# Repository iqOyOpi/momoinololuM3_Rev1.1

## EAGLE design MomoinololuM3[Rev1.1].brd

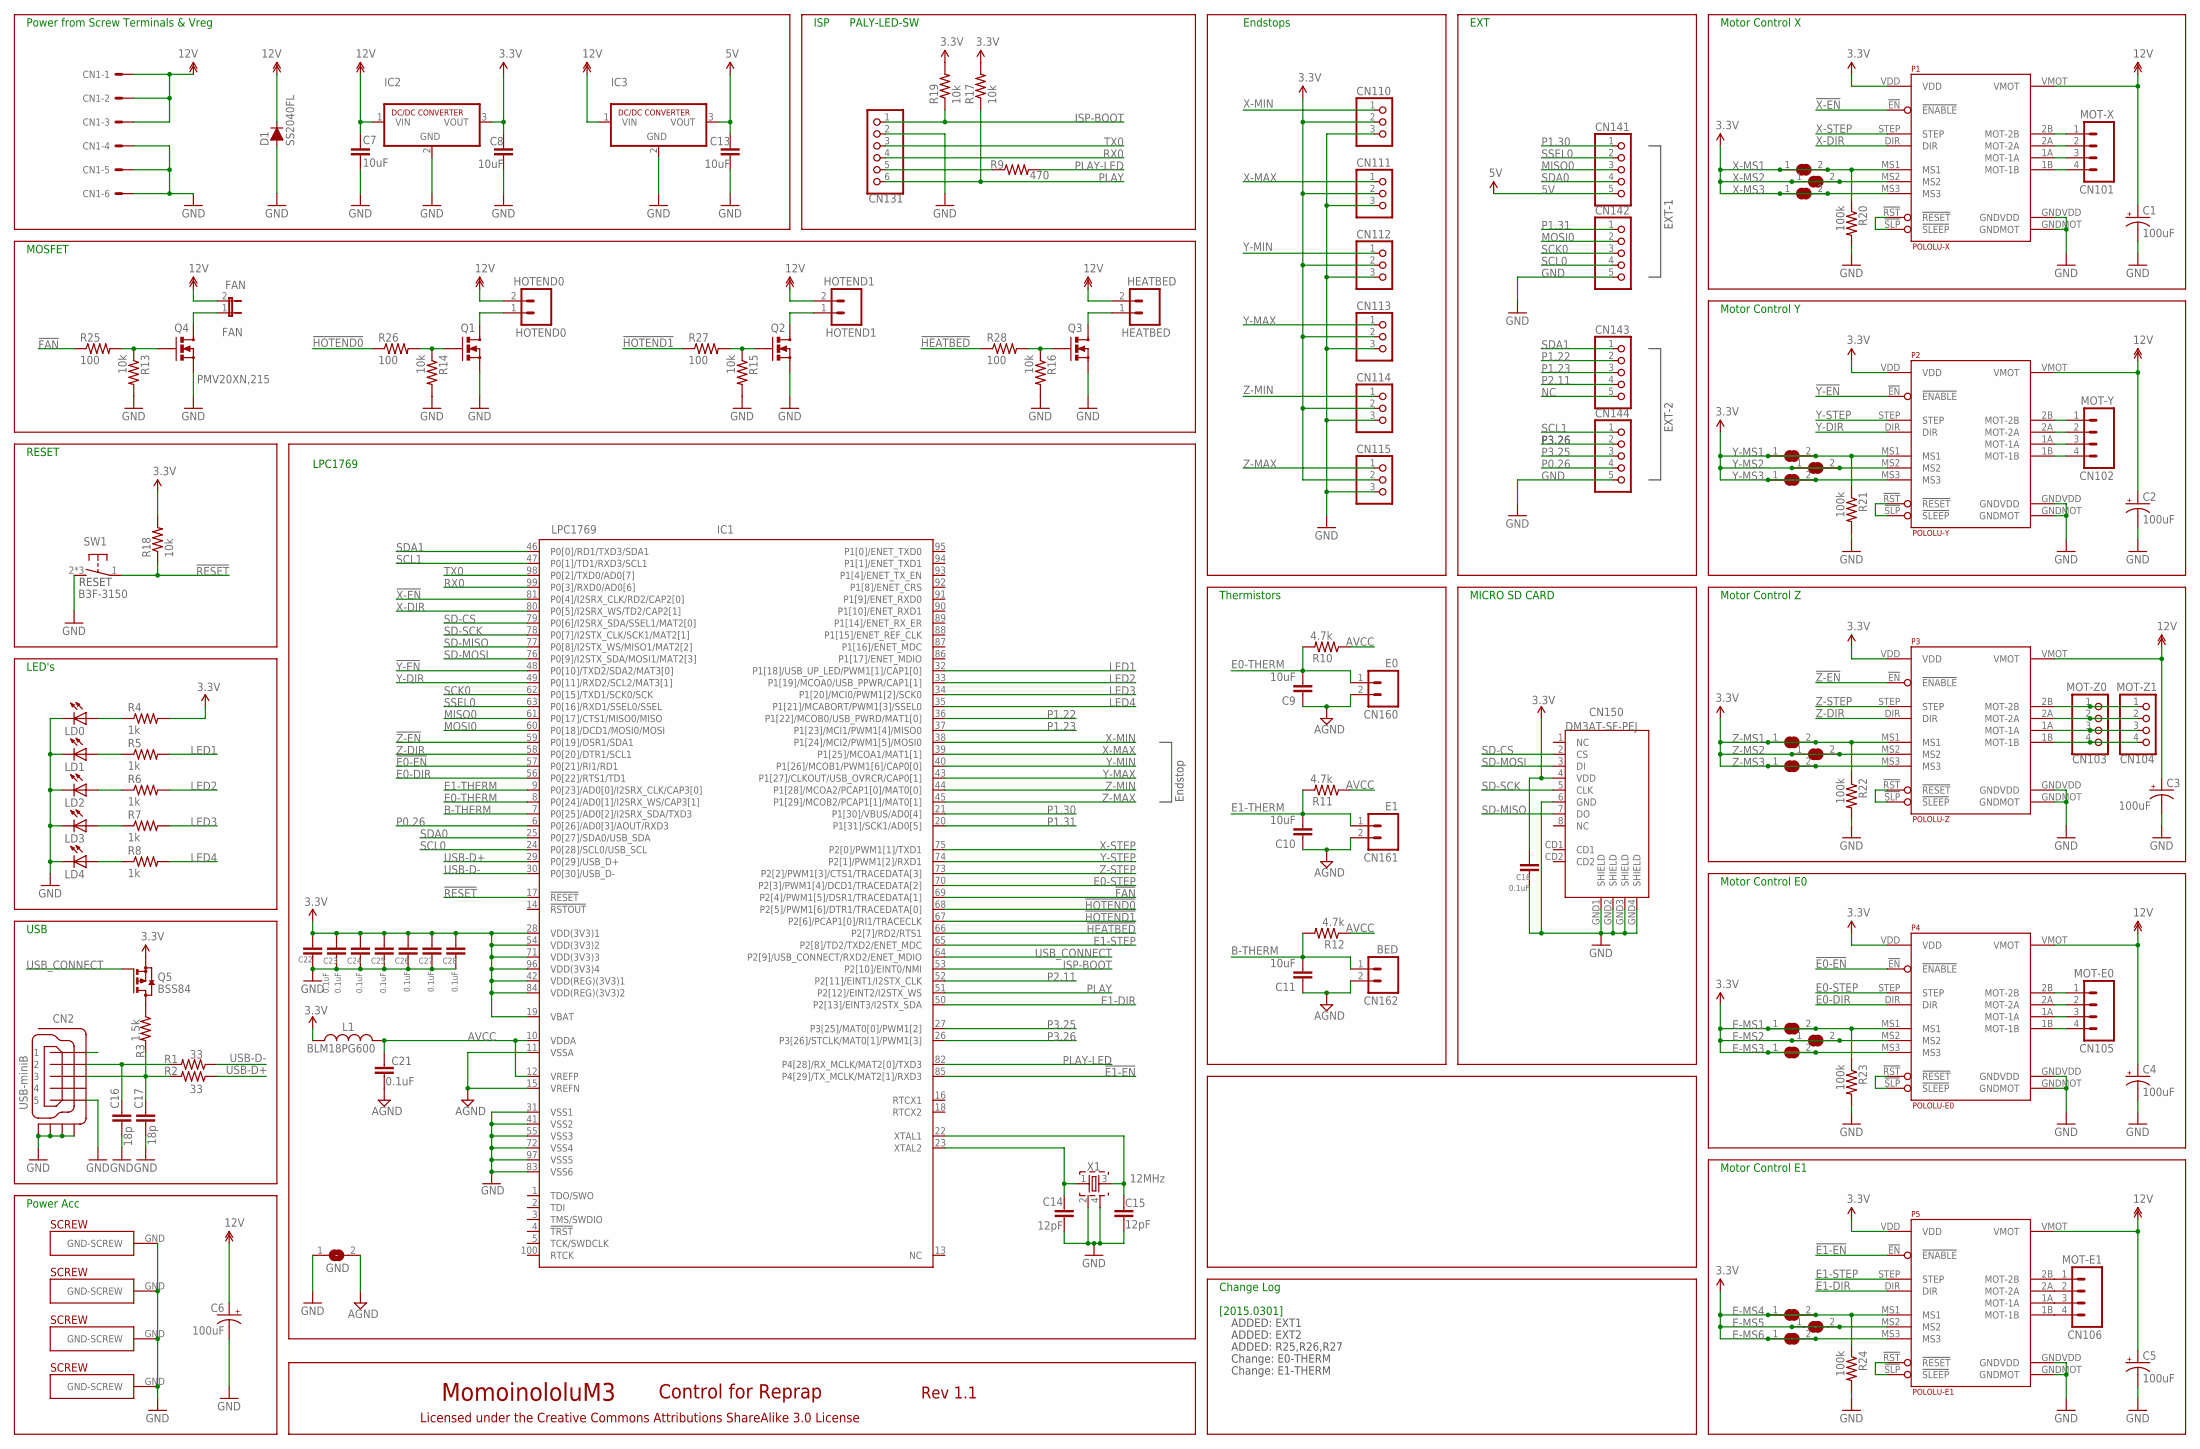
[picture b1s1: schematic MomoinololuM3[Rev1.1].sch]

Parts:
C1, C2, C3, C4, C5, C6: 100uF; UD-6,3X7,7_NICHICON
C7, C8, C9, C10, C11, C13: 10uF; RCL_C1206K
C14, C15: 12pF; C0603
C16, C17: 18p; C0603
C18, C21, C22, C23, C24, C25, C26, C27, C28: 0.1uF; C0603
CN1: 556X-6H; 5569-6
CN2: USB-miniB; CON-HIROSE_UX60A-MB-5ST
CN101: MOT-X; SPARKFUN_MOLEX-1X4
CN102: MOT-Y; SPARKFUN_MOLEX-1X4
CN103: MOT-Z0; 1X04
CN104: MOT-Z1; 1X04
CN105: MOT-E0; SPARKFUN_MOLEX-1X4
CN106: MOT-E1; SPARKFUN_MOLEX-1X4
CN110, CN111, CN112, CN113, CN114, CN115: PINHD-1X3; 1X03
CN131: PINHD-1X6; 1X06
CN141, CN142, CN143, CN144: PINHD-1X5; 1X05
CN150: DM3AT-SF-PEJ
CN160: E0; SPARKFUN_1X02
CN161: E1; SPARKFUN_1X02
CN162: BED; SPARKFUN_1X02
D1: SS2040FL; SEMICON-SMD-IPC_SOD123
E-MS1, E-MS2, E-MS3, E-MS4, E-MS5, E-MS6: SJ
FAN: FAN; SPARKFUN_1X02
GND: SJ
HEATBED: HEATBED; SCREWTERMINAL-5.08MM-2
HOLE1, HOLE2, HOLE3, HOLE4: PLATED-SCREW; PLATEDSCREW
HOTEND0: HOTEND0; SCREWTERMINAL-5.08MM-2
HOTEND1: HOTEND1; SCREWTERMINAL-5.08MM-2
IC1: LPC1769; LQFP100-14X14
IC2: R-78E3.3-0.5; SIP3
IC3: R-78E5.0-0.5; SIP3
L1: BLM18PG600; L2012C
LD0, LD1, LD2, LD3, LD4: LEDSML0805; SML0805
P1: POLOLU-X; POLOLU-ALLEGRO_POLOLU-ALLEGRO-PTH
P2: POLOLU-Y; POLOLU-ALLEGRO_POLOLU-ALLEGRO-PTH
P3: POLOLU-Z; POLOLU-ALLEGRO_POLOLU-ALLEGRO-PTH
P4: POLOLU-E0; POLOLU-ALLEGRO_POLOLU-ALLEGRO-PTH
P5: POLOLU-E1; POLOLU-ALLEGRO_POLOLU-ALLEGRO-PTH
Q1, Q2, Q3: PSMN038-100YLX; SOT669
Q4: PMV20XN,215; SPARKFUN_SOT23-3
Q5: BSS84; SOT23
R1, R2: 33; R0603
R3: 1.5k; R0603
R4, R5, R6, R7, R8: 1k; R0603
R9: 470; R0603
R10, R11, R12: 4.7k; R0603
R13, R14, R15, R16, R17, R18, R19: 10k; R0603
R20, R21, R22, R23, R24: 100k; R0603
R25, R26, R27, R28: 100; R0603
SW1: B3F-3150; B3F-31XX
X1: 12MHz; FA-238
X-MS1, X-MS2, X-MS3: SJ
Y-MS1, Y-MS2, Y-MS3: SJ
Z-MS1, Z-MS2, Z-MS3: SJ

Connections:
3.3V: C8.1, C18.2, C22.2, C23.2, C24.2, C25.2, C26.2, C27.2, C28.2, CN110.2, CN111.2, CN112.2, CN113.2, CN114.2, CN115.2, CN150.4 (VDD), E-MS1.1, E-MS1.2, E-MS2.1, E-MS2.2, E-MS3.1, E-MS3.2, E-MS4.1, E-MS4.2, E-MS5.1, E-MS5.2, E-MS6.1, E-MS6.2, IC1.19 (VBAT), IC1.28 (VDD(3V3)1), IC1.42 (VDD(REG)(3V3)1), IC1.54 (VDD(3V3)2), IC1.71 (VDD(3V3)3), IC1.84 (VDD(REG)(3V3)2), IC1.96 (VDD(3V3)4), IC2.3 (VOUT), L1.1, P1.MS1, P1.MS2, P1.MS3, P1.VDD, P2.MS1, P2.MS2, P2.MS3, P2.VDD, P3.MS1, P3.MS2, P3.MS3, P3.VDD, P4.MS1, P4.MS2, P4.MS3, P4.VDD, P5.MS1, P5.MS2, P5.MS3, P5.VDD, Q5.2 (S), R4.2, R17.2, R18.2, R19.2, R20.1, R21.1, R22.1, R23.1, R24.1, X-MS1.1, X-MS1.2, X-MS2.1, X-MS2.2, X-MS3.1, X-MS3.2, Y-MS1.1, Y-MS1.2, Y-MS2.1, Y-MS2.2, Y-MS3.1, Y-MS3.2, Z-MS1.1, Z-MS1.2, Z-MS2.1, Z-MS2.2, Z-MS3.1, Z-MS3.2
5V: C13.1, CN141.5, IC3.3 (VOUT)
12V: C1.+, C2.+, C3.+, C4.+, C5.+, C6.+, C7.1, CN1.1, CN1.2, CN1.3, D1.1 (C), FAN.2, HEATBED.2, HOTEND0.2, HOTEND1.2, IC2.1 (VIN), IC3.1 (VIN), P1.VMOT, P2.VMOT, P3.VMOT, P4.VMOT, P5.VMOT
!E0-EN: IC1.57 (P0[21]/RI1/RD1), P4.!EN (!ENABLE)
!E1-EN: IC1.85 (P4[29]/TX_MCLK/MAT2[1]/RXD3), P5.!EN (!ENABLE)
!FAN: IC1.69 (P2[4]/PWM1[5]/DSR1/TRACEDATA[1]), R25.1
!HEATBED: IC1.66 (P2[7]/RD2/RTS1), R28.1
!HOTEND0: IC1.68 (P2[5]/PWM1[6]/DTR1/TRACEDATA[0]), R26.1
!HOTEND1: IC1.67 (P2[6]/PCAP1[0]/RI1/TRACECLK), R27.1
!RESET: IC1.17 (!RESET), R18.1, SW1.1
!X-EN: IC1.81 (P0[4]/I2SRX_CLK/RD2/CAP2[0]), P1.!EN (!ENABLE)
!Y-EN: IC1.48 (P0[10]/TXD2/SDA2/MAT3[0]), P2.!EN (!ENABLE)
!Z-EN: IC1.59 (P0[19]/DSR1/SDA1), P3.!EN (!ENABLE)
AGND: C9.1, C10.1, C11.1, C21.2, CN160.2, CN161.2, CN162.2, GND.2, IC1.11 (VSSA), IC1.15 (VREFN)
AVCC: C21.1, IC1.10 (VDDA), IC1.12 (VREFP), L1.2, R10.1, R11.1, R12.1
B-THERM: C11.2, CN162.1, IC1.7 (P0[25]/AD0[2]/I2SRX_SDA/TXD3), R12.2
E0-DIR: IC1.56 (P0[22]/RTS1/TD1), P4.DIR
E0-STEP: IC1.70 (P2[3]/PWM1[4]/DCD1/TRACEDATA[2]), P4.STEP
E0-THERM: C9.2, CN160.1, IC1.8 (P0[24]/AD0[1]/I2SRX_WS/CAP3[1]), R10.2
E1-DIR: IC1.50 (P2[13]/EINT3/I2STX_SDA), P5.DIR
E1-STEP: IC1.65 (P2[8]/TD2/TXD2/ENET_MDC), P5.STEP
E1-THERM: C10.2, CN161.1, IC1.9 (P0[23]/AD0[0]/I2SRX_CLK/CAP3[0]), R11.2
E-MOT-1A: CN105.3, P4.1A (MOT-1A)
E-MOT-1A1: CN106.3, P5.1A (MOT-1A)
E-MOT-1B: CN105.4, P4.1B (MOT-1B)
E-MOT-1B1: CN106.4, P5.1B (MOT-1B)
E-MOT-2A: CN105.2, P4.2A (MOT-2A)
E-MOT-2A1: CN106.2, P5.2A (MOT-2A)
E-MOT-2B: CN105.1, P4.2B (MOT-2B)
E-MOT-2B1: CN106.1, P5.2B (MOT-2B)
E-RESETSLEEP: P4.!RST (!RESET), P4.!SLP (!SLEEP)
E-RESETSLEEP1: P5.!RST (!RESET), P5.!SLP (!SLEEP)
GND: C1.-, C2.-, C3.-, C4.-, C5.-, C6.-, C7.2, C8.2, C13.2, C14.2, C15.2, C16.2, C17.2, C18.1, C22.1, C23.1, C24.1, C25.1, C26.1, C27.1, C28.1, CN1.4, CN1.5, CN1.6, CN2.5, CN2.M1 (S1), CN2.M2 (S2), CN2.M3 (S3), CN2.M4 (S4), CN110.3, CN111.3, CN112.3, CN113.3, CN114.3, CN115.3, CN131.2, CN142.5, CN144.5, CN150.6 (GND), CN150.GND1 (SHIELD), CN150.GND2 (SHIELD), CN150.GND3 (SHIELD), CN150.GND4 (SHIELD), D1.2 (A), GND.1, HOLE1.GND, HOLE2.GND, HOLE3.GND, HOLE4.GND, IC1.31 (VSS1), IC1.41 (VSS2), IC1.55 (VSS3), IC1.72 (VSS4), IC1.83 (VSS6), IC1.97 (VSS5), IC2.2 (GND), IC3.2 (GND), LD0.C, LD1.C, LD2.C, LD3.C, LD4.C, P1.GNDMOT, P1.GNDVDD, P2.GNDMOT, P2.GNDVDD, P3.GNDMOT, P3.GNDVDD, P4.GNDMOT, P4.GNDVDD, P5.GNDMOT, P5.GNDVDD, Q1.1 (S), Q1.2 (S), Q1.3 (S), Q2.1 (S), Q2.2 (S), Q2.3 (S), Q3.1 (S), Q3.2 (S), Q3.3 (S), Q4.2 (S), R13.2, R14.2, R15.2, R16.2, R20.2, R21.2, R22.2, R23.2, R24.2, SW1.2 (S), SW1.3 (S), SW1.4 (S), X1.2, X1.4
HEATBED-GND: HEATBED.1, Q3.MB (D)
HOTEND0-GND: HOTEND0.1, Q1.MB (D)
HOTEND-GND1: HOTEND1.1, Q2.MB (D)
ISP-BOOT: CN131.1, IC1.53 (P2[10]/EINT0/NMI), R19.1
LED0: LD0.A, R4.1
LED1: IC1.32 (P1[18]/USB_UP_LED/PWM1[1]/CAP1[0]), R5.2
LED2: IC1.33 (P1[19]/MCOA0/USB_PPWR/CAP1[1]), R6.2
LED3: IC1.34 (P1[20]/MCI0/PWM1[2]/SCK0), R7.2
LED4: IC1.35 (P1[21]/MCABORT/PWM1[3]/SSEL0), R8.2
MISO0: CN141.3, IC1.61 (P0[17]/CTS1/MISO0/MISO)
MOSI0: CN142.2, IC1.60 (P0[18]/DCD1/MOSI0/MOSI)
unnamed: Q5.3 (D), R3.1
unnamed: Q4.1 (G), R13.1, R25.2
unnamed: Q1.4 (G), R14.1, R26.2
unnamed: FAN.1, Q4.3 (D)
unnamed: C16.1, CN2.2, R1.2
unnamed: C17.1, CN2.3, R2.2, R3.2
unnamed: Q2.4 (G), R15.1, R27.2
unnamed: CN131.5, R9.1
unnamed: LD1.A, R5.1
unnamed: LD2.A, R6.1
unnamed: LD3.A, R7.1
unnamed: LD4.A, R8.1
unnamed: Q3.4 (G), R16.1, R28.2
NC: CN143.5
P0.26: CN144.4, IC1.6 (P0[26]/AD0[3]/AOUT/RXD3)
P1.22: CN143.2, IC1.36 (P1[22]/MCOB0/USB_PWRD/MAT1[0])
P1.23: CN143.3, IC1.37 (P1[23]/MCI1/PWM1[4]/MISO0)
P1.30: CN141.1, IC1.21 (P1[30]/VBUS/AD0[4])
P1.31: CN142.1, IC1.20 (P1[31]/SCK1/AD0[5])
P2.11: CN143.4, IC1.52 (P2[11]/EINT1/I2STX_CLK)
P3.25: CN144.3, IC1.27 (P3[25]/MAT0[0]/PWM1[2])
P3.26: CN144.2, IC1.26 (P3[26]/STCLK/MAT0[1]/PWM1[3])
PLAY: CN131.6, IC1.51 (P2[12]/EINT2/I2STX_WS), R17.1
PLAY-LED: IC1.82 (P4[28]/RX_MCLK/MAT2[0]/TXD3), R9.2
RX0: CN131.4, IC1.99 (P0[3]/RXD0/AD0[6])
SCK0: CN142.3, IC1.62 (P0[15]/TXD1/SCK0/SCK)
SCL0: CN142.4, IC1.24 (P0[28]/SCL0/USB_SCL)
SCL1: CN144.1, IC1.47 (P0[1]/TD1/RXD3/SCL1)
SD-CS: CN150.2 (CS), IC1.79 (P0[6]/I2SRX_SDA/SSEL1/MAT2[0])
SD-MISO: CN150.7 (DO), IC1.77 (P0[8]/I2STX_WS/MISO1/MAT2[2])
SD-MOSI: CN150.3 (DI), IC1.76 (P0[9]/I2STX_SDA/MOSI1/MAT2[3])
SD-SCK: CN150.5 (CLK), IC1.78 (P0[7]/I2STX_CLK/SCK1/MAT2[1])
SDA0: CN141.4, IC1.25 (P0[27]/SDA0/USB_SDA)
SDA1: CN143.1, IC1.46 (P0[0]/RD1/TXD3/SDA1)
SSEL0: CN141.2, IC1.63 (P0[16]/RXD1/SSEL0/SSEL)
TX0: CN131.3, IC1.98 (P0[2]/TXD0/AD0[7])
USB-D+: IC1.29 (P0[29]/USB_D+), R2.1
USB-D-: IC1.30 (P0[30]/USB_D-), R1.1
USB_CONNECT: IC1.64 (P2[9]/USB_CONNECT/RXD2/ENET_MDIO), Q5.1 (G)
VBUS: CN2.1
X'TAL-IN: C15.1, IC1.22 (XTAL1), X1.3
X'TAL-OUT: C14.1, IC1.23 (XTAL2), X1.1
X-DIR: IC1.80 (P0[5]/I2SRX_WS/TD2/CAP2[1]), P1.DIR
X-MAX: CN111.1, IC1.39 (P1[25]/MCOA1/MAT1[1])
X-MIN: CN110.1, IC1.38 (P1[24]/MCI2/PWM1[5]/MOSI0)
X-MOT-1A: CN101.3, P1.1A (MOT-1A)
X-MOT-1B: CN101.4, P1.1B (MOT-1B)
X-MOT-2A: CN101.2, P1.2A (MOT-2A)
X-MOT-2B: CN101.1, P1.2B (MOT-2B)
X-RESETSLEEP: P1.!RST (!RESET), P1.!SLP (!SLEEP)
X-STEP: IC1.75 (P2[0]/PWM1[1]/TXD1), P1.STEP
Y-DIR: IC1.49 (P0[11]/RXD2/SCL2/MAT3[1]), P2.DIR
Y-MAX: CN113.1, IC1.43 (P1[27]/CLKOUT/USB_OVRCR/CAP0[1])
Y-MIN: CN112.1, IC1.40 (P1[26]/MCOB1/PWM1[6]/CAP0[0])
Y-MOT-1A: CN102.3, P2.1A (MOT-1A)
Y-MOT-1B: CN102.4, P2.1B (MOT-1B)
Y-MOT-2A: CN102.2, P2.2A (MOT-2A)
Y-MOT-2B: CN102.1, P2.2B (MOT-2B)
Y-RESETSLEEP: P2.!RST (!RESET), P2.!SLP (!SLEEP)
Y-STEP: IC1.74 (P2[1]/PWM1[2]/RXD1), P2.STEP
Z-DIR: IC1.58 (P0[20]/DTR1/SCL1), P3.DIR
Z-MAX: CN115.1, IC1.45 (P1[29]/MCOB2/PCAP1[1]/MAT0[1])
Z-MIN: CN114.1, IC1.44 (P1[28]/MCOA2/PCAP1[0]/MAT0[0])
Z-MOT-1A: CN103.3, CN104.3, P3.1A (MOT-1A)
Z-MOT-1B: CN103.4, CN104.4, P3.1B (MOT-1B)
Z-MOT-2A: CN103.2, CN104.2, P3.2A (MOT-2A)
Z-MOT-2B: CN103.1, CN104.1, P3.2B (MOT-2B)
Z-RESETSLEEP: P3.!RST (!RESET), P3.!SLP (!SLEEP)
Z-STEP: IC1.73 (P2[2]/PWM1[3]/CTS1/TRACEDATA[3]), P3.STEP

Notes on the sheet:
Motor Control X
Motor Control Y
Motor Control Z
Motor Control E0
Thermistors
Endstops
LPC1769
USB
MOSFET
Power Acc
MomoinololuM3
Rev 1.1
Control for Reprap
Licensed under the Creative Commons Attributions ShareAlike 3.0 License
Power from Screw Terminals & Vreg
RESET
Motor Control E1
ISP
Endstop
LED's
MICRO SD CARD
PALY-LED-SW
EXT
EXT-1
EXT-2
Change Log
ADDED: EXT1
ADDED: EXT2
Change: E0-THERM
ADDED: R25,R26,R27
Change: E1-THERM
[2015.0301]

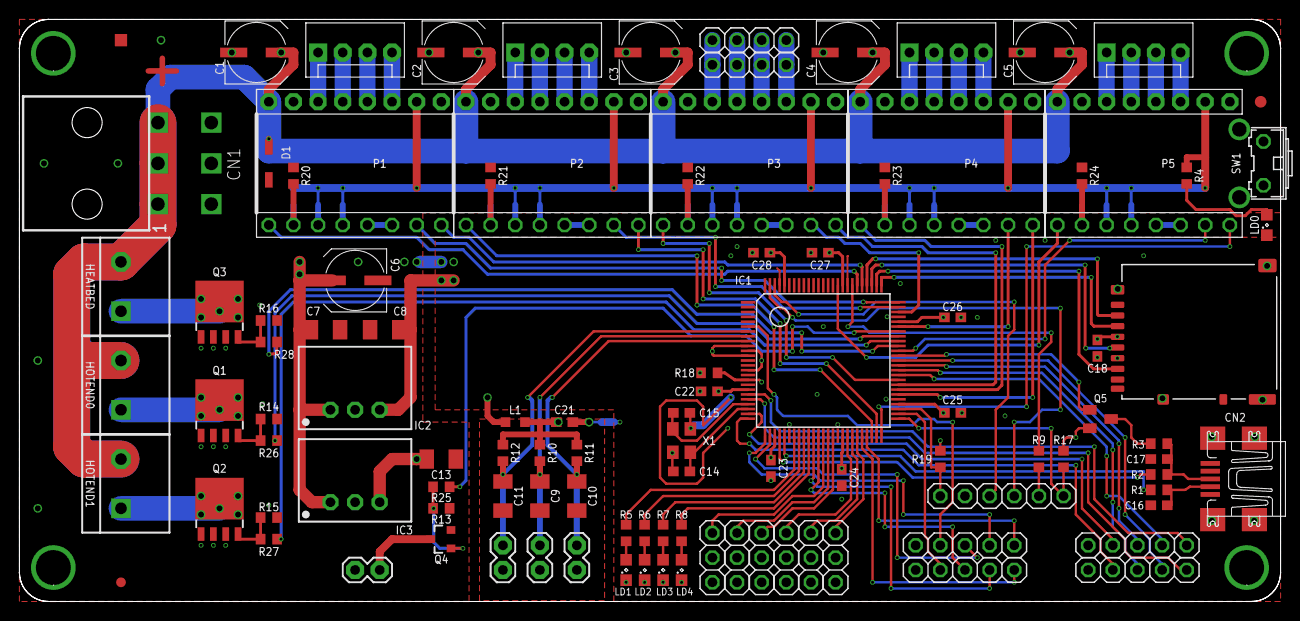
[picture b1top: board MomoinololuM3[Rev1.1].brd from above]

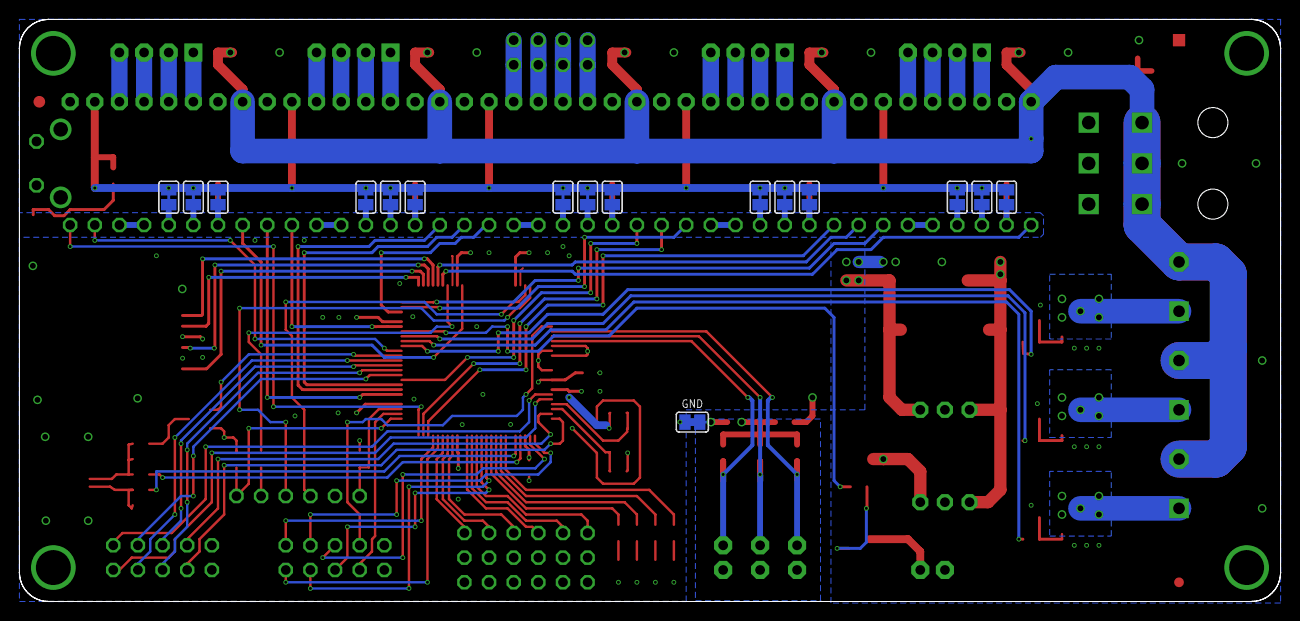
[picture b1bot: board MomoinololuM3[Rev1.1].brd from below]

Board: 4 copper layers, 130.0 x 60.0 mm, 122 parts (16 on the bottom side), 111 nets.

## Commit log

2015-08-21 :octocat: Added .gitattributes & .gitignore files
2015-08-21 New Commit!
